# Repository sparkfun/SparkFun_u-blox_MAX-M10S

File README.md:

SparkFun GNSS Receiver Breakout - MAX-M10S (Qwiic)
===========================================================

[*SparkFun GNSS Receiver Breakout - MAX-M10S (Qwiic) (GPS-18037)*](https://www.sparkfun.com/products/18037)

The SparkFun MAX-M10S Breakout is an ultra-low-power, high performance, miniaturized GNSS board that is perfect for battery operated applications that don't possess a lot of space, such as asset trackers and wearable devices. The MAX-M10S module from u-blox has an extremely low power consumption that is less than 25mW in continuous tracking mode.

The on-board MAX-M10S GNSS receiver can receive signals from the GPS, GLONASS, BeiDou, and Galileo constellations. Thanks to the u-blox Super-S technology, the module offers improved RF sensitivity with small antennas and in non-line-of-sight scenarios. We've included an SMA connector for a sturdy connection when attaching an external antenna. The board is also equipped with an on-board rechargeable battery that provides backup power to the module's RTC. This reduces the time-to-first fix from a cold start (~24s) to a hot start (~1s). The battery will maintain RTC and GNSS orbit data without being connected to power for up to five hours. This increases precision and decreases lock time in battery operated devices without compromising GNSS performance.

Additionally, this u-blox receiver supports I2C which makes it perfect for Qwiic compatibility so we don't have to use up our precious UART ports. Utilizing our handy Qwiic system, no soldering is required to connect it to the rest of your system. However, we still broke out 0.1"-spaced pins in case you prefer to use a breadboard. For users that prefer to communicate over UART, we made sure to configure the UART pin grouping to an industry standard to ensure that it easily connects to a Serial Basic.

U-blox based GNSS products are configurable using the popular Windows program called u-center. Plenty of different functions can be configured on the MAX-M10S: baud rates, update rates, spoofing detection, external interrupts, etc. We've also written an extensive Arduino library for u-blox modules to make reading and controlling the MAX-M10S over our Qwiic Connect System easy. Leave NMEA behind! Start using a much lighter weight binary interface and give your microcontroller (and its one serial port) a break. The SparkFun Arduino library shows how to read latitude, longitude, even heading and speed over I2C without the need for constant serial polling.

Repository Contents
-------------------

* **/Documents** - Related U-blox datasheets and various whitepapers 
* **/Hardware** - Eagle files

Documentation
--------------

* **[Installing an Arduino Library Guide](https://learn.sparkfun.com/tutorials/installing-an-arduino-library)** - Basic information on how to install an Arduino library.
* **[Arduino Library](https://github.com/sparkfun/SparkFun_u-blox_GNSS_Arduino_Library)** - Arduino Library for u-blox modules.
* **[Hookup Guide](https://learn.sparkfun.com/tutorials/1759)** - Hookup guide for the SparkFun GNSS Receiver Breakout - MAX-M10S (Qwiic).

Product Versions
----------------
* [GPS-18037](https://www.sparkfun.com/products/18037)

Version History
---------------
* v1.0 - Initial Release

License Information
-------------------

This product is _**open source**_! 

Various bits of the code have different licenses applied. Anything SparkFun wrote is beerware; if you see me (or any other SparkFun employee) at the local, and you've found our code helpful, please buy us a round!

Please use, reuse, and modify these files as you see fit. Please maintain attribution to SparkFun Electronics and release anything derivative under the same license.

Distributed as-is; no warranty is given.

- Your friends at SparkFun.

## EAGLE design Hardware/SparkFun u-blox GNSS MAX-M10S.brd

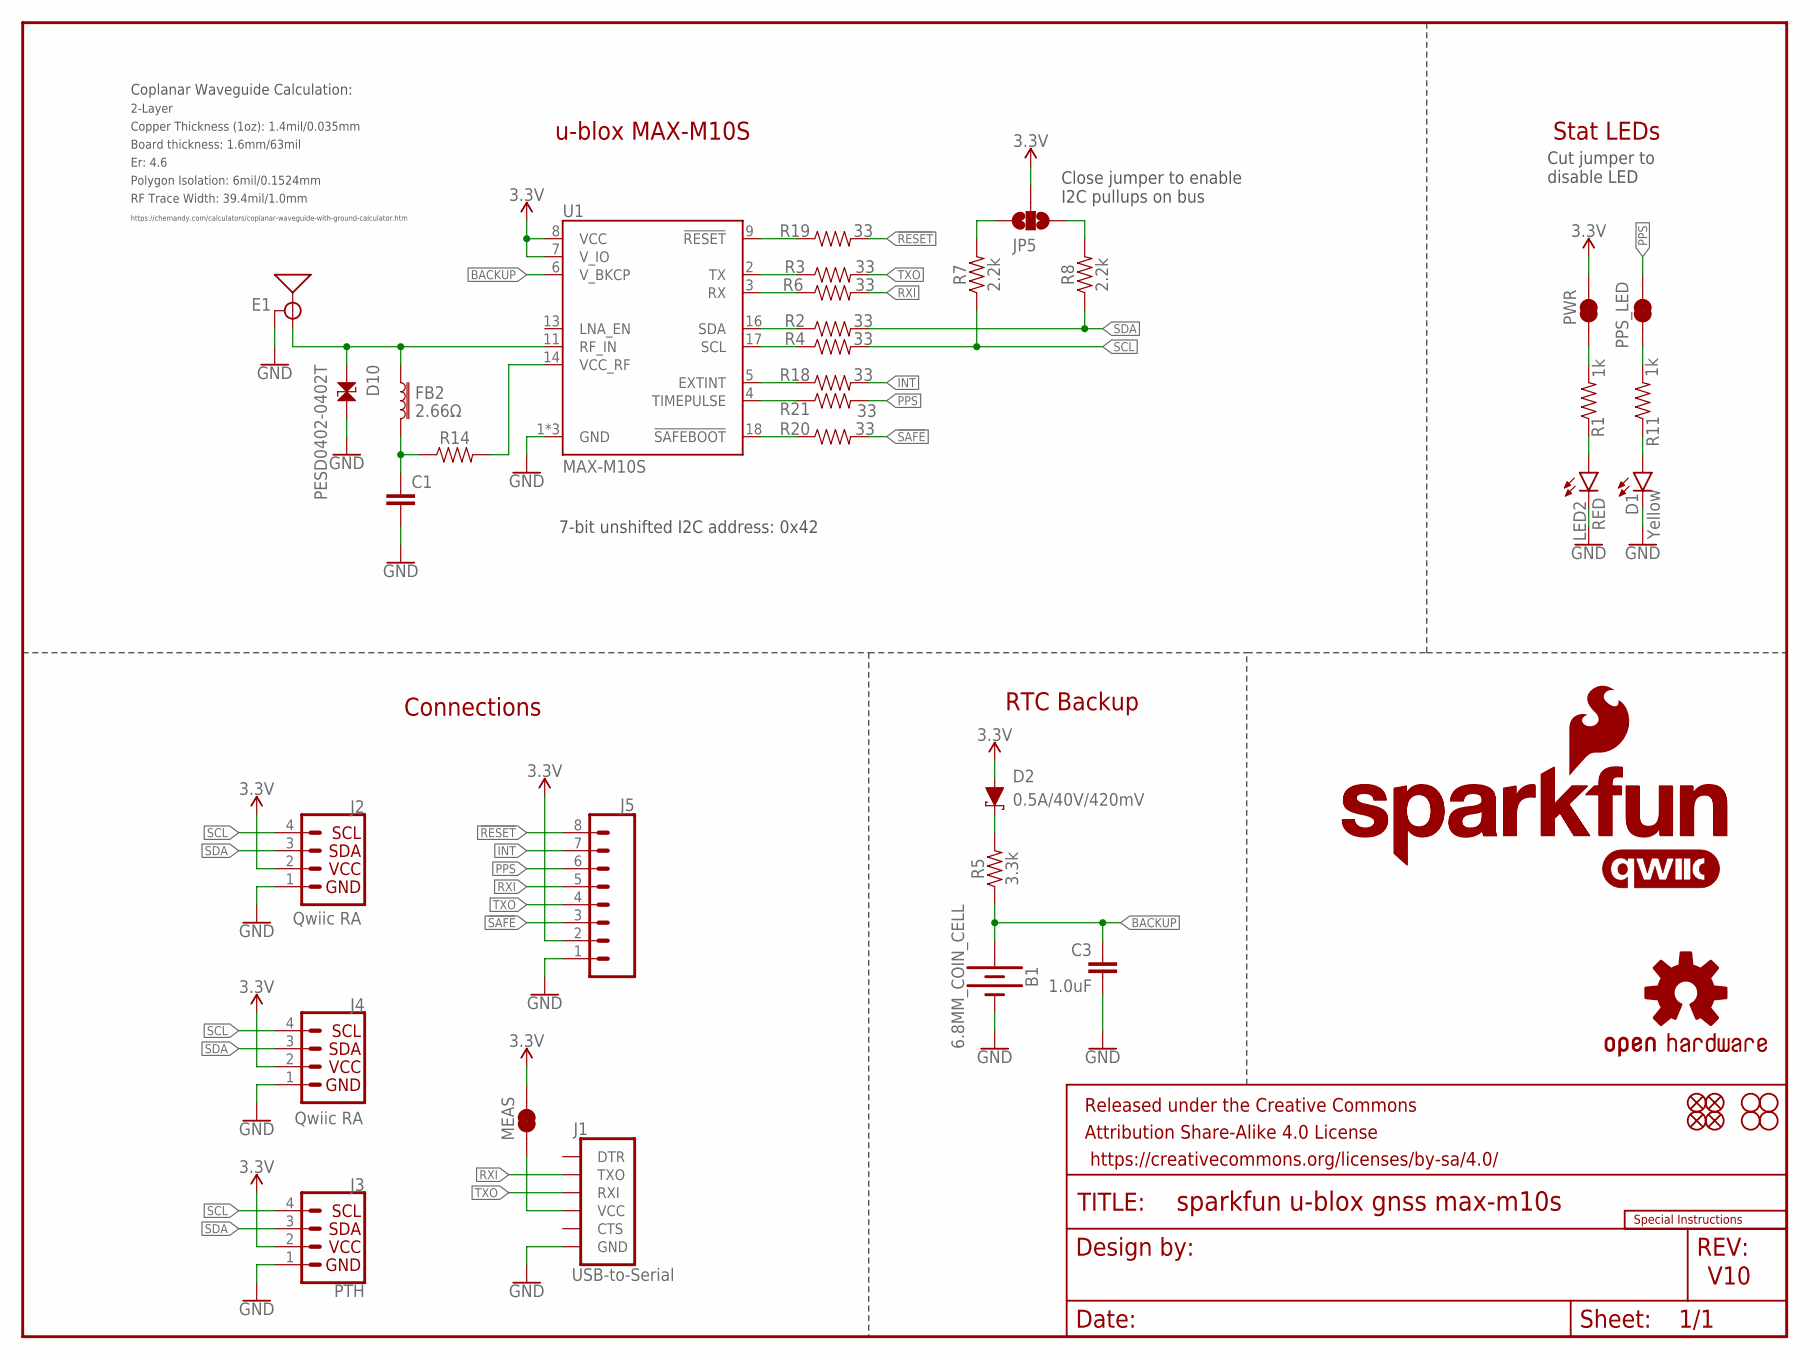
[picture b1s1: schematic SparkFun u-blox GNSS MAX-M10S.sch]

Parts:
B1: 6.8MM_COIN_CELL; ML414H_IV01E
C1: 47pF; 0402-TIGHT
C3: 1.0uF; 0603
D1: Yellow; LED-0603
D2: 0.5A/40V/420mV; SOD-323
D10: PESD0402-0402T; 0402-TIGHT
E1: ANTENNA-SMA-GROUNDEDEDGE_SMA; SMA-EDGE
FB2: 2.66Ω; 0402-TIGHT
FD1, FD2, FD3, FD4: FIDUCIALUFIDUCIAL; FIDUCIAL-MICRO
FRAME1: FRAME-LETTER; CREATIVE_COMMONS
H1, H2, H3, H4: STAND-OFF
J1: USB-to-Serial; 1X06_NO_SILK
J2, J4: Qwiic RA; JST04_1MM_RA
J3: PTH; 1X04_NO_SILK
J5: CONN_08NO_SILK_DNP; 1X08_NO_SILK
JP5: JUMPER-SMT_3_NO_SILK; SMT-JUMPER_3_NO_SILK
LED2: RED; LED-0603
LOGO1: OSHW-LOGOMINI; OSHW-LOGO-MINI
LOGO2: SFE_LOGO_NAME_FLAME.1_INCH; SFE_LOGO_NAME_FLAME_.1
LOGO3: QWIIC_LOGO_5MM; QWIIC_5MM
LOGO4: SFE_LOGO_NAME.1_INCH; SFE_LOGO_NAME_.1
MEAS: JUMPER-COMBO_2_NC_TRACE; COMBO-JUMPER_2_NC_TRACE
PPS_LED: JUMPER-SMT_2_NC_TRACE_SILK; SMT-JUMPER_2_NC_TRACE_SILK
PWR: JUMPER-SMT_2_NC_TRACE_SILK; SMT-JUMPER_2_NC_TRACE_SILK
R1, R11: 1k; 0603
R2, R3, R4, R6, R18, R19, R20, R21: 33; 0603
R5: 3.3k; 0603
R7, R8: 2.2k; 0603
R14: 33OHM-0402T-1/10W-1%; 0402-TIGHT
U1: MAX-M10S
U$2: SPECIAL_INSTRUCTIONS-ORDERING; ORDERING_INSTRUCTIONS

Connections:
3.3V: D2.A, J2.2, J3.2 (VCC), J4.2, J5.2, JP5.2, MEAS.2, MEAS.4 (2), PWR.2, U1.7 (V_IO), U1.8 (VCC)
!RESET: J5.8, R19.2
!SAFE: J5.3, R20.2
ANT_VCC: C1.1, FB2.2, R14.1
BACKUP: B1.+, C3.1, R5.1, U1.6 (V_BKCP)
EXTINT_LV: R18.1, U1.5 (EXTINT)
GND: B1.-, C1.2, C3.2, D1.C, D10.2, E1.GND@0 (GND), E1.GND@1 (GND), E1.GND@2 (GND), E1.GND@3 (GND), J1.6 (GND), J2.1, J3.1 (GND), J4.1, J5.1, LED2.C, U1.1 (GND), U1.10 (GND), U1.12 (GND)
GPS_RF: D10.1, E1.SIG (SIGNAL), FB2.1, U1.11 (RF_IN)
INT: J5.7, R18.2
unnamed: J1.4 (VCC), MEAS.1, MEAS.3 (1)
unnamed: D1.A, R11.1
unnamed: PPS_LED.1, R11.2
unnamed: JP5.1, R8.2
unnamed: D2.C, R5.2
unnamed: JP5.3, R7.2
unnamed: LED2.A, R1.1
unnamed: PWR.1, R1.2
PPS: J5.6, PPS_LED.2, R21.2
PPS_LV: R21.1, U1.4 (TIMEPULSE)
RST_LV: R19.1, U1.9 (!RESET!)
RXI: J1.3 (TXO), J5.5, R6.2
RXLV: R6.1, U1.3 (RX)
SAFE_LV: R20.1, U1.18 (!SAFEBOOT!)
SCL: J2.4, J3.4 (SCL), J4.4, R4.2, R7.1
SCL_LV: R4.1, U1.17 (SCL)
SDA: J2.3, J3.3 (SDA), J4.3, R2.2, R8.1
SDA_LV: R2.1, U1.16 (SDA)
TXLV: R3.1, U1.2 (TX)
TXO: J1.2 (RXI), J5.4, R3.2
VCC_RF: R14.2, U1.14 (VCC_RF)

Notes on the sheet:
V10
7-bit unshifted I2C address: 0x42
u-blox MAX-M10S
RTC Backup
Stat LEDs
Close jumper to enable I2C pullups on bus
Cut jumper to disable LED
Coplanar Waveguide Calculation:
Connections
Board thickness: 1.6mm/63mil
Er: 4.6
Copper Thickness (1oz): 1.4mil/0.035mm
RF Trace Width: 39.4mil/1.0mm
Polygon Isolation: 6mil/0.1524mm
2-Layer
https://chemandy.com/calculators/coplanar-waveguide-with-ground-calculator.htm

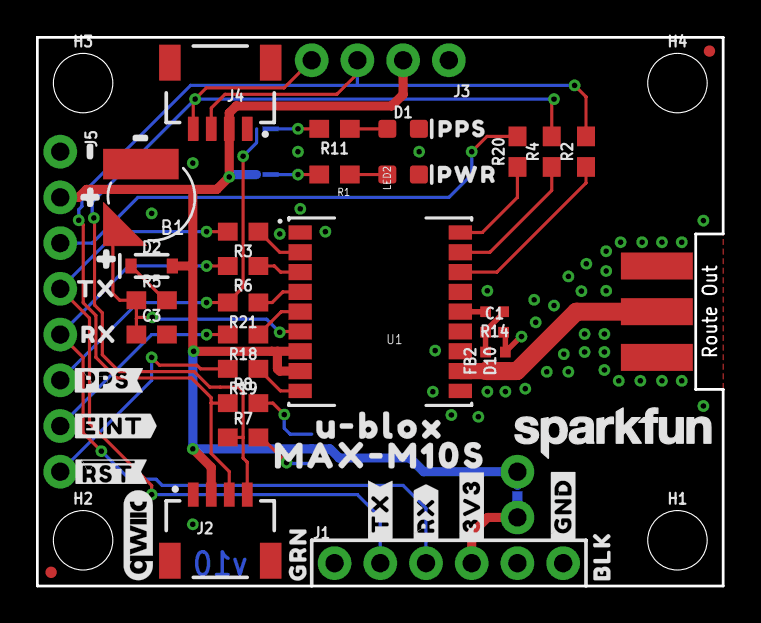
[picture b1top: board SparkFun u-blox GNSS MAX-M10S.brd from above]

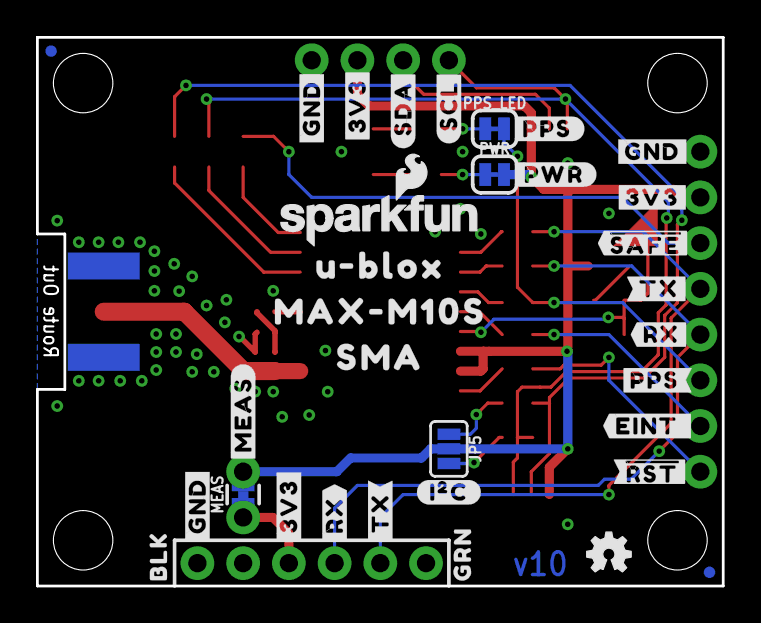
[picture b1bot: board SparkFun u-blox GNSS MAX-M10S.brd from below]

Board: 2 copper layers, 38.1 x 30.5 mm, 91 parts (33 on the bottom side), 30 nets.

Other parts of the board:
U$1, U$10, U$26, U$31: #3V3#4
U$3, U$11, U$27, U$34: #GND#5
U$4, U$28: BLK0
U$5, U$29: GRN1
U$6: PPS7
U$7: PWR6
U$8, U$25: #RX#2
U$9, U$22: #TX#3
U$12: ##RST##2
U$13: ##SAFE##0
U$14, U$43: #PPS#1
U$15: #RX#1
U$16: #TX#0
U$18, U$23: MAX#M10S1
U$19, U$37: #0
U$20, U$21: U#BLOX0
U$24: SMA2
U$30: #I�C#0
U$32: #SCL#1
U$33: #SDA#0
U$35: #PPS#0
U$36: #PWR#0
U$38, U$40: #1
U$39: ##RST##0
U$41: #MEAS#0
U$42: #EINT#0
U$44: RX2
U$45: TX3
U$46: #EINT_#0

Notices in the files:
parts and their libraries:
SparkFun-Resistors: Licensing: Creative Commons ShareAlike 4.0 International - https://creativecommons.org/licenses/by-sa/4.0
SparkFun-Aesthetics: Released under the Creative Commons Attribution Share-Alike 4.0 License
SparkFun-Aesthetics: https://creativecommons.org/licenses/by-sa/4.0
